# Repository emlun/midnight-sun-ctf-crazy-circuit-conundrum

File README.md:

"Crazy Circuit Conundrum" challenge for Midnight Sun CTF 2018
---

This repository contains the scripts and schematics used to create the "Crazy
Circuit Conundrum" challenge for [Midnight Sun CTF 2018][midnight-sun]. A build
log for the project can be found [here][build-log].

The `code v1` and `code v2` directories can both be opened as projects in
[KiCad][kicad].

All files in this repository are licensed under a [Creative Commons
Attribution 4.0 International License][cc] unless noted otherwise.

[build-log]: https://emlun.se/2018/06/17/build-log-the-crazy-circuit-conundrum-for-midnight-sun-ctf
[cc]: https://creativecommons.org/licenses/by/4.0/
[kicad]: http://kicad-pcb.org/
[midnight-sun]: https://www.midnightsunctf.se/

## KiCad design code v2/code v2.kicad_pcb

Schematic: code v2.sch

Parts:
BT1: Battery_Cell; Battery_holder_2xAA
D1, D2: LED; LED_D5.0mm
D3: LED; LED_D10.0mm
J1: PWR-2_pole_power_connector; J2x2-double_2_pole_connector
Q1, Q2, Q3, Q4: 2N7000; TO-92_Molded_Wide_Inline
R1, R2, R3, R4, R5, R6, R7, R8, R9, R10, R11, R12, R13, R14, R15, R16, R17, R18, R19: R; R_Axial_DIN0204_L3.6mm_D1.6mm_P5.08mm_Vertical
SW1, SW2: SW_DIP_x08; SW_DIP_x8_W7.62mm_Slide
U1, U2, U3: 74HC04; DIP-14_W7.62mm_Socket
U4, U5: 74LS08; DIP-14_W7.62mm_Socket
U6, U7: 74HCT02; DIP-14_W7.62mm_Socket
U8, U9: 4068B_8_AND; DIP-14_W7.62mm_Socket

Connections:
/i0: R1.2, SW1.16, U1.1
/i1: R2.2, SW1.15, U1.3, U4.12
/i2: R3.2, SW1.14, U1.5
/i3: R4.2, SW1.13, U1.9
/i4: R5.2, SW1.12, U1.11, U4.4
/i5: R6.2, SW1.11, U1.13, U5.13
/i6: R7.2, SW1.10, U2.1, U4.9
/i7: R8.2, SW1.9, U2.3, U7.13
/i8: R9.2, SW2.16, U2.5
/i9: R10.2, SW2.15, U7.9, U7.12
/i10: R11.2, SW2.14, U2.9, U4.2
/i11: R12.2, SW2.13, U2.11
/i12: R13.2, SW2.12, U2.13, U6.13
/i13: R14.2, SW2.11, U3.1
/i14: R15.2, SW2.10, U3.3, U4.5
/i15: R16.2, SW2.9, U3.5
/not_i0: U1.2, U4.13, U5.1
/not_i1: U1.4, U6.8
/not_i2: U1.6, U5.2, U5.4
/not_i3: U1.8, U5.10, U5.12
/not_i4: U1.10, U6.1
/not_i5: U1.12, U6.5
/not_i6: U2.2, U6.2
/not_i7: U2.4, U4.1
/not_i8: U2.6, U7.2, U7.5
/not_i10: U2.8, U6.6
/not_i11: U2.10, U6.9, U6.12
/not_i12: U2.12, U4.10
/not_i13: U3.2, U7.6, U7.8
/not_i14: U3.4, U7.1
/not_i15: U3.6, U5.5, U5.9
unnamed: D1.1 (K), Q1.3 (D)
unnamed: D1.2 (A), R17.2
unnamed: D2.1 (K), Q2.3 (D)
unnamed: D2.2 (A), R18.2
unnamed: D3.1 (K), Q3.3 (D)
unnamed 36: D3.2 (A), R19.2; also elsewhere on the board
unnamed: Q1.2 (G), Q4.2 (G), U8.1 (K)
unnamed: Q2.2 (G), Q3.2 (G), U9.1 (K)
unnamed: Q3.1 (S), Q4.3 (D)
unnamed: U4.3, U8.2 (A)
unnamed: U4.6, U8.3 (B)
unnamed: U4.8, U8.4 (C)
unnamed: U4.11, U8.5 (D)
unnamed: U5.3, U8.9 (E)
unnamed: U5.6, U8.10 (F)
unnamed: U5.8, U8.11 (G)
unnamed: U5.11, U8.12 (H)
unnamed: U6.3, U9.2 (A)
unnamed: U6.4, U9.3 (B)
unnamed: U6.10, U9.4 (C)
unnamed: U6.11, U9.5 (D)
unnamed: U7.3, U9.9 (E)
unnamed: U7.4, U9.10 (F)
unnamed: U7.10, U9.11 (G)
unnamed: U7.11, U9.12 (H)

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
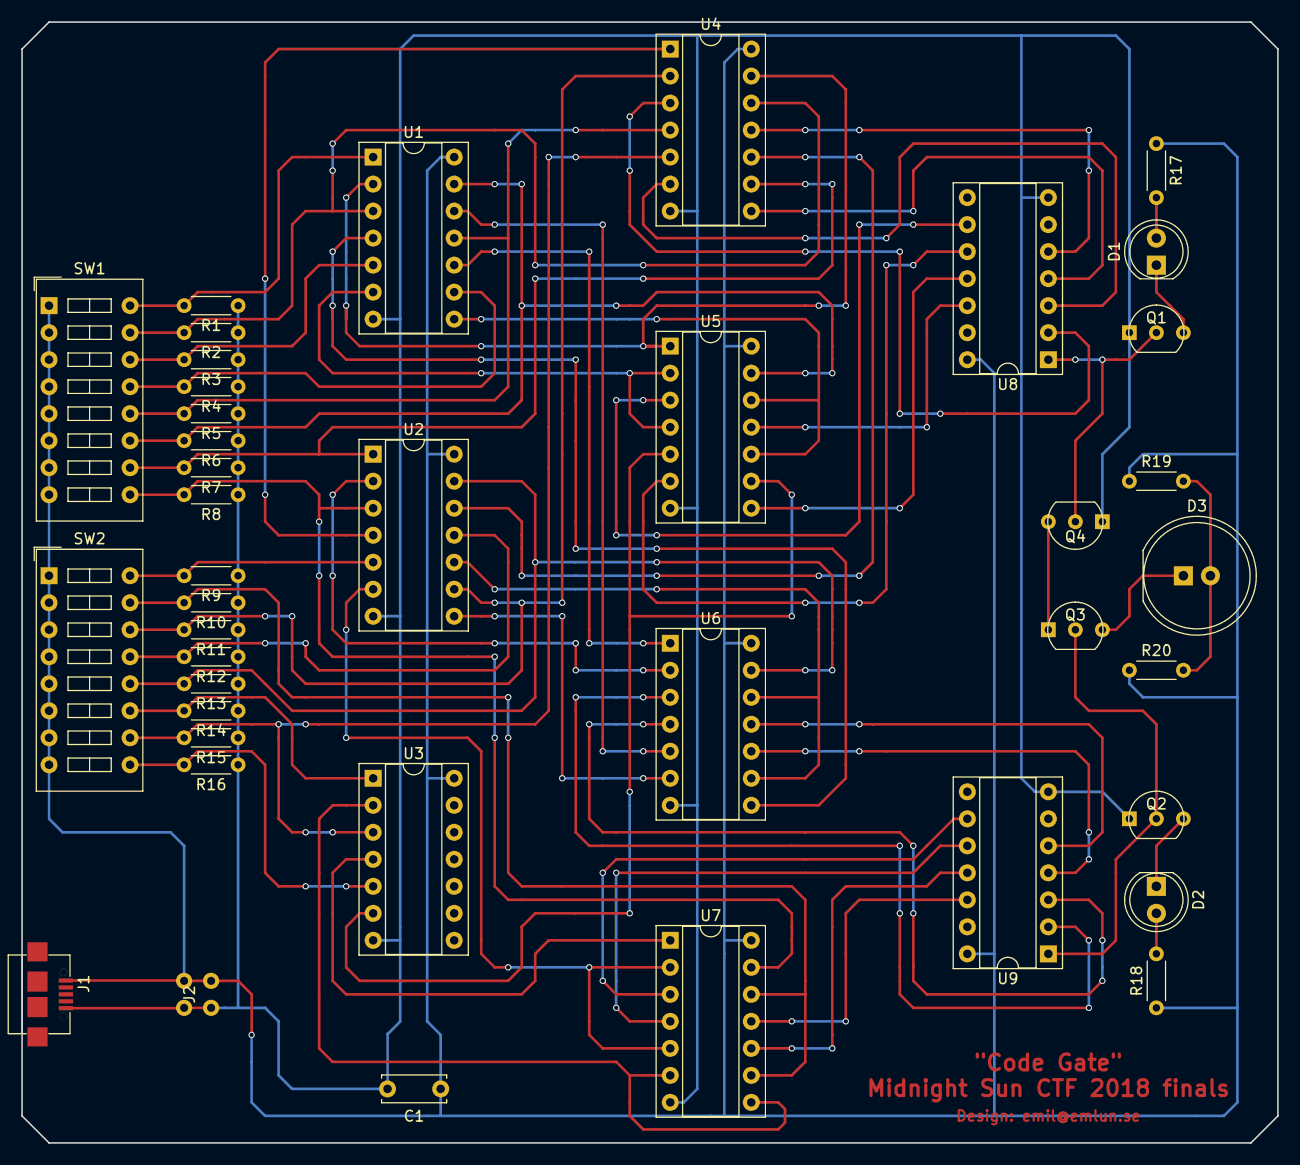
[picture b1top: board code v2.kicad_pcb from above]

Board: 2 copper layers, 118.1 x 105.4 mm, 41 parts (0 on the bottom side), 58 nets.

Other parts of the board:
C1: C; C_Disc_D6.0mm_W2.5mm_P5.00mm
J2: PWR-2_pole_power_connector; J2x2-double_2_pole_connector
R20: R; R_Axial_DIN0204_L3.6mm_D1.6mm_P5.08mm_Horizontal

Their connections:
unnamed 36: R20.2; also elsewhere on the board

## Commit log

2018-06-03 Initial commit
    There will be many others
    But this one is first
2018-06-03 Add Boolean formula generator script
2018-06-03 Make generator script build a problem iteratively instead of randomly
2018-06-03 Add selected solution
2018-06-03 Move KiCad project into subdirectory
2018-06-05 Add code circuit v2
2018-06-11 Add finished PCB design
2018-06-11 Finish some more
2018-06-16 Add README and licenses
